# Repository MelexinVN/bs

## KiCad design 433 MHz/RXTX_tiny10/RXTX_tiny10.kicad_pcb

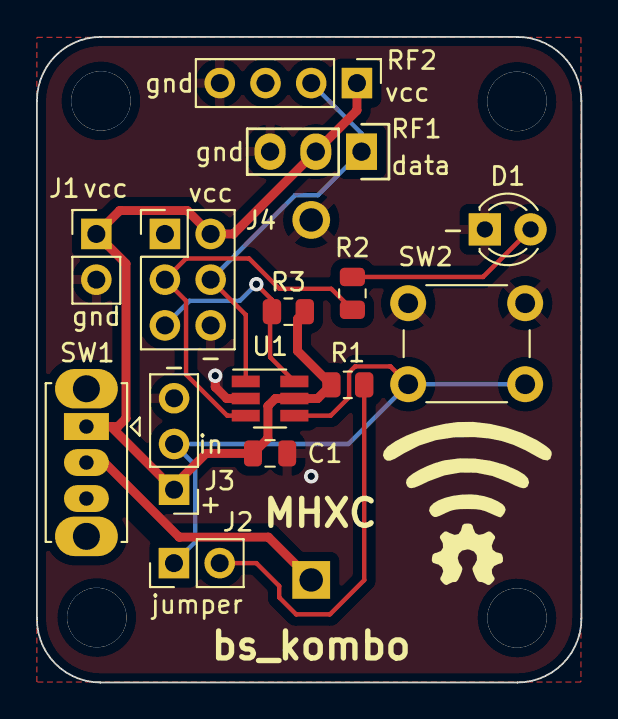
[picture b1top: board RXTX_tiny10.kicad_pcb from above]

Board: 2 copper layers, 30.3 x 35.9 mm, 15 parts (1 on the bottom side), 9 nets.

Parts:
BT?: Battery_Cell; BatteryHolder_ComfortableElectronic_CH273-2450_1x2450
C1: 100n; C_0805_2012Metric
D1: SFH4346; LED_D3.0mm
J1, J1#2: Conn_01x02; PinHeader_1x02_P2.54mm_Vertical
J3: Conn_01x03; PinHeader_1x03_P2.54mm_Vertical
J?: AVR-ISP-6; PinHeader_2x03_P2.54mm_Vertical
R?: 4.7K; R_0805_2012Metric
R?#2, R?#3: 4.7K; R_0805_2012Metric
RF1: RF_Transmitter_433_MHz
RF2: RF_Receiver_433_MHz; PinHeader_1x04_P2.54mm_Vertical
SW1: SW_DPDT_x2; SW_Slide_1P2T_CK_OS102011MS2Q
SW2: SW_Push_Dual_x2; SW_PUSH_6mm_H4.3mm
U1: ATtiny10-TS; SOT-23-6_Handsoldering

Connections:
+3V3: C1.1, J1#2.1, J3.1, J?.2 (VCC), R?.2, R?#2.2, RF1.2 (VCC), RF2.1 (VCC), SW1.1 (A), U1.5 (VCC)
GND: BT?.2 (-), C1.2, D1.1 (K), J1#2.2, J3.3, J?.6 (GND), RF1.3 (GND), RF2.4 (GND), SW2.2 (D), U1.2 (GND)
unnamed: BT?.1 (+), SW1.2 (B)
unnamed: D1.2 (A), R?#3.1
unnamed: J1.1, J3.2, SW2.1 (C), U1.4 (PB2)
unnamed: J1.2, R?.1
unnamed: J?.3 (SCK), R?#3.2, U1.3 (PB1)
unnamed: J?.4 (MOSI), RF1.1 (DATA), RF2.2 (DATA), U1.1 (PB0)
unnamed: J?.5 (~RST), R?#2.1, U1.6 (~RESET/PB3)

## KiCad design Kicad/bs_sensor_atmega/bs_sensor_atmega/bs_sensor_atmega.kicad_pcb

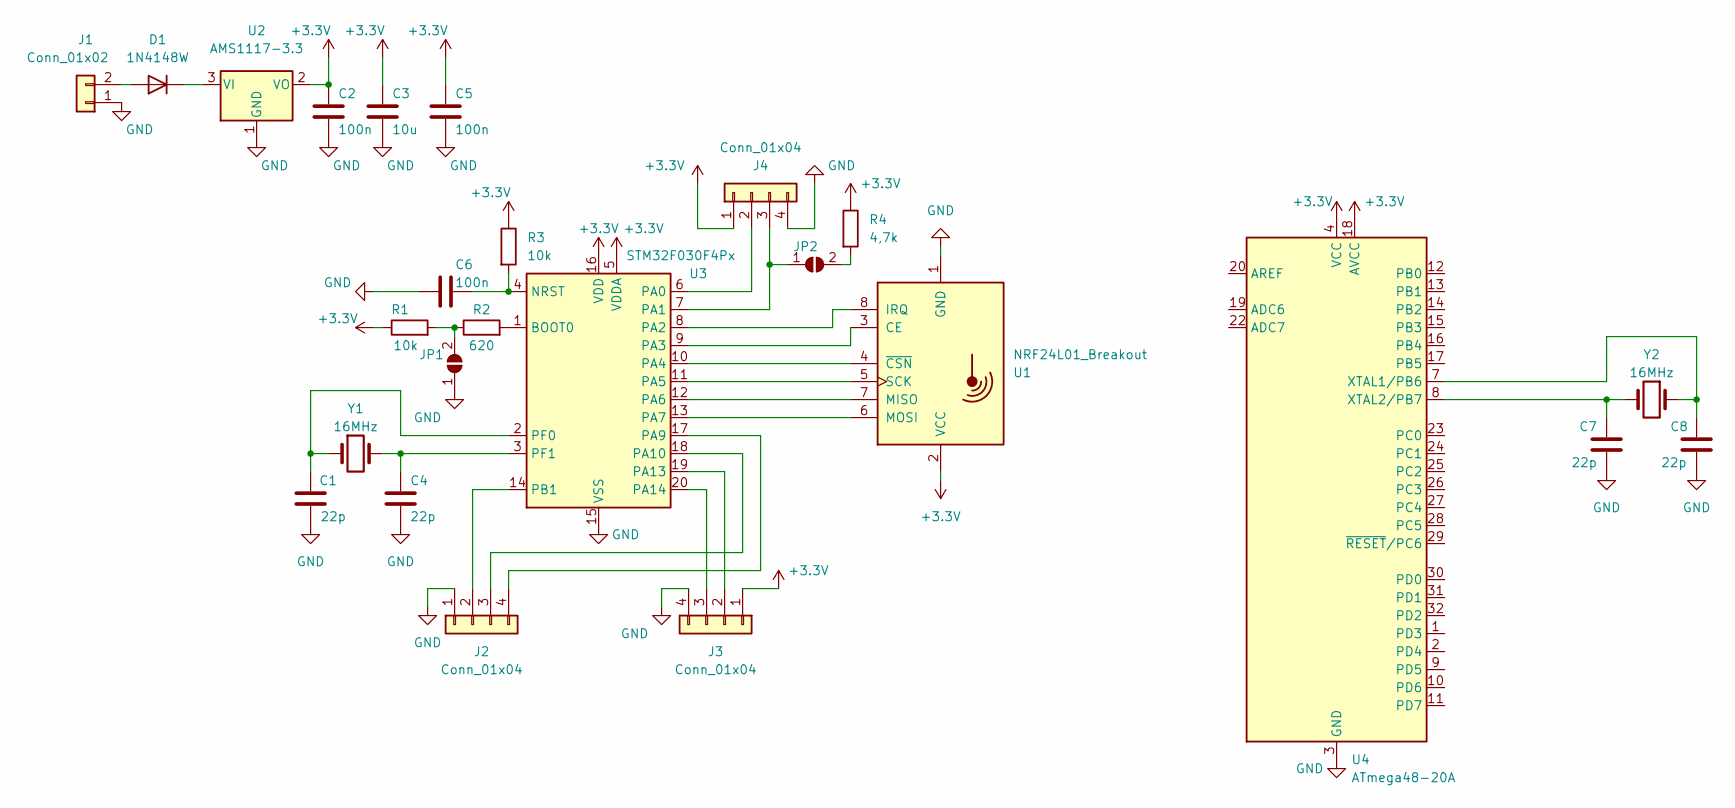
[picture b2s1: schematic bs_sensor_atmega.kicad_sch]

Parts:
C1, C4, C7, C8: 22p; C_0805_2012Metric
C2, C5, C6: 100n; C_0805_2012Metric
C3: 10u; C_0805_2012Metric
D1: 1N4148W; D_SOD-123
J1: Conn_01x02; PinHeader_1x02_P2.54mm_Vertical
J2, J3, J4: Conn_01x04; PinHeader_1x04_P2.54mm_Vertical
JP1, JP2: SolderJumper_2_Open; SolderJumper-2_P1.3mm_Open_TrianglePad1.0x1.5mm
R1, R3: 10k; R_0805_2012Metric
R2: 620; R_0603_1608Metric
R4: 4,7k; R_0805_2012Metric
U1: NRF24L01_Breakout; nRF24L01_Breakout
U2: AMS1117-3.3; SOT-223-3_TabPin2
U3: STM32F030F4Px; TSSOP-20_4.4x6.5mm_P0.65mm
U4: ATmega48-20A; TQFP-32_7x7mm_P0.8mm
Y1, Y2: 16MHz; Crystal_HC49-U_Vertical

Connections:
+3V3: C2.1, C3.1, C5.1, J3.1, J4.1, R1.1, R3.1, R4.1, U1.2 (VCC), U2.2 (VO), U3.5 (VDDA), U3.16 (VDD), U4.4 (VCC), U4.6 (VCC), U4.18 (AVCC)
GND: C1.1, C2.2, C3.2, C4.2, C5.2, C6.2, C7.2, C8.1, J1.1, J2.1, J3.4, J4.4, JP1.1 (A), U1.1 (GND), U2.1 (GND), U3.15 (VSS), U4.3 (GND), U4.5 (GND), U4.21 (GND)
unnamed: C1.2, U3.2 (PF0), Y1.1
unnamed: C4.1, U3.3 (PF1), Y1.2
unnamed: C6.1, R3.2, U3.4 (NRST)
unnamed: C7.1, U4.8 (XTAL2/PB7), Y2.2
unnamed: C8.2, U4.7 (XTAL1/PB6), Y2.1
unnamed: D1.1 (K), U2.3 (VI)
unnamed: D1.2 (A), J1.2
unnamed: J2.2, U3.14 (PB1)
unnamed: J2.3, U3.18 (PA10)
unnamed: J2.4, U3.17 (PA9)
unnamed: J3.2, U3.19 (PA13)
unnamed: J3.3, U3.20 (PA14)
unnamed: J4.2, U3.6 (PA0)
unnamed: J4.3, JP2.1 (A), U3.7 (PA1)
unnamed: JP1.2 (B), R1.2, R2.1
unnamed: JP2.2 (B), R4.2
unnamed: R2.2, U3.1 (BOOT0)
unnamed: U1.3 (CE), U3.9 (PA3)
unnamed: U1.4 (~CSN), U3.10 (PA4)
unnamed: U1.5 (SCK), U3.11 (PA5)
unnamed: U1.6 (MOSI), U3.13 (PA7)
unnamed: U1.7 (MISO), U3.12 (PA6)
unnamed: U1.8 (IRQ), U3.8 (PA2)

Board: 2 copper layers, 25 parts (0 on the bottom side), 25 nets, no tracks yet.

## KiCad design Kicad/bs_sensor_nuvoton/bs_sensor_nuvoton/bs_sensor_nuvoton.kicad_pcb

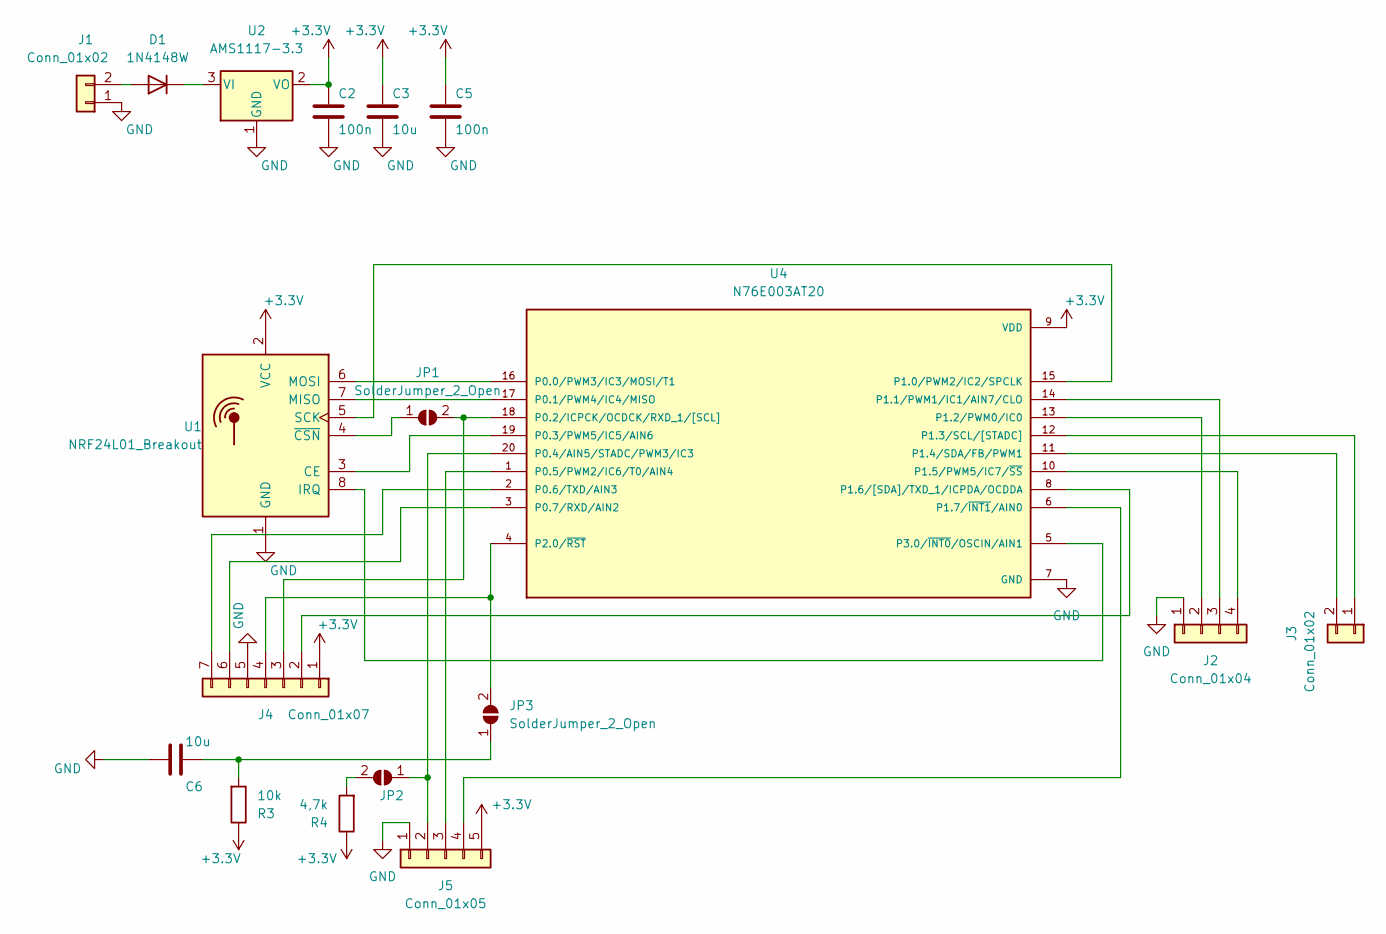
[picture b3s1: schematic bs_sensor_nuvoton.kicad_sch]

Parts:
C2, C5: 100n; C_0805_2012Metric
C3, C6: 10u; C_0805_2012Metric
D1: 1N4148W; D_SOD-123
J1, J3: Conn_01x02; PinHeader_1x02_P2.54mm_Vertical
J2: Conn_01x04; PinHeader_1x04_P2.54mm_Vertical
J4: Conn_01x07; PinHeader_1x07_P2.54mm_Vertical
J5: Conn_01x05; PinHeader_1x05_P2.54mm_Vertical
JP1, JP2, JP3: SolderJumper_2_Open; SolderJumper-2_P1.3mm_Open_TrianglePad1.0x1.5mm
R3: 10k; R_0805_2012Metric
R4: 4,7k; R_0805_2012Metric
U1: NRF24L01_Breakout; nRF24L01_Breakout
U2: AMS1117-3.3; SOT-223-3_TabPin2
U4: N76E003AT20; SOP65P640X120-20N; PARTREV 1.04

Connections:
+3V3: C2.1, C3.1, C5.1, J4.1, J5.5, R3.1, R4.1, U1.2 (VCC), U2.2 (VO), U4.9 (VDD)
GND: C2.2, C3.2, C5.2, C6.2, J1.1, J2.1, J4.5, J5.1, U1.1 (GND), U2.1 (GND), U4.7 (GND)
unnamed: C6.1, JP3.1 (A), R3.2
unnamed: D1.1 (K), U2.3 (VI)
unnamed: D1.2 (A), J1.2
unnamed: J2.2, U4.13 (P1.2/PWM0/IC0)
unnamed: J2.3, U4.14 (P1.1/PWM1/IC1/AIN7/CLO)
unnamed: J2.4, U4.10 (P1.5/PWM5/IC7/~SS)
unnamed: J3.1, U4.12 (P1.3/SCL/[STADC])
unnamed: J3.2, U4.11 (P1.4/SDA/FB/PWM1)
unnamed: J4.2, U4.8 (P1.6/[SDA]/TXD_1/ICPDA/OCDDA)
unnamed: J4.3, JP1.2 (B), U4.18 (P0.2/ICPCK/OCDCK/RXD_1/[SCL])
unnamed: J4.4, JP3.2 (B), U4.4 (P2.0/~RST)
unnamed: J4.6, U4.3 (P0.7/RXD/AIN2)
unnamed: J4.7, U4.2 (P0.6/TXD/AIN3)
unnamed: J5.2, JP2.1 (A), U4.20 (P0.4/AIN5/STADC/PWM3/IC3)
unnamed: J5.3, U4.1 (P0.5/PWM2/IC6/T0/AIN4)
unnamed: J5.4, U4.6 (P1.7/~INT1/AIN0)
unnamed: JP1.1 (A), U1.4 (~CSN)
unnamed: JP2.2 (B), R4.2
unnamed: U1.3 (CE), U4.19 (P0.3/PWM5/IC5/AIN6)
unnamed: U1.5 (SCK), U4.15 (P1.0/PWM2/IC2/SPCLK)
unnamed: U1.6 (MOSI), U4.16 (P0.0/PWM3/IC3/MOSI/T1)
unnamed: U1.7 (MISO), U4.17 (P0.1/PWM4/IC4/MISO)
unnamed: U1.8 (IRQ), U4.5 (P3.0/~INT0/OSCIN/AIN1)

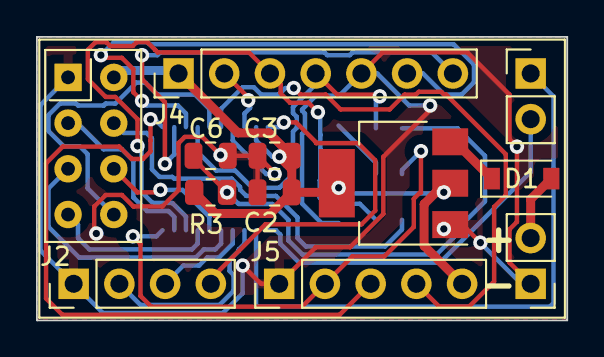
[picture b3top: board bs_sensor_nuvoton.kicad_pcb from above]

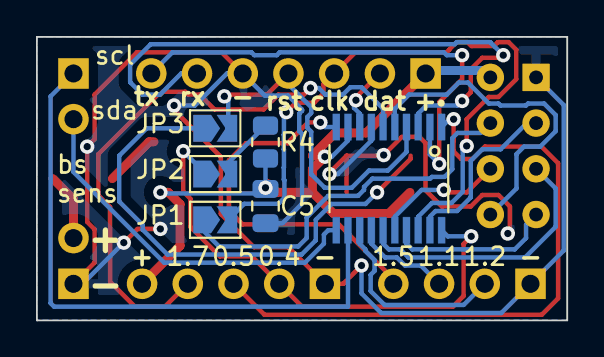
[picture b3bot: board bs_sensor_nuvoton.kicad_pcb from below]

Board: 2 copper layers, 29.5 x 15.7 mm, 18 parts (6 on the bottom side), 25 nets.

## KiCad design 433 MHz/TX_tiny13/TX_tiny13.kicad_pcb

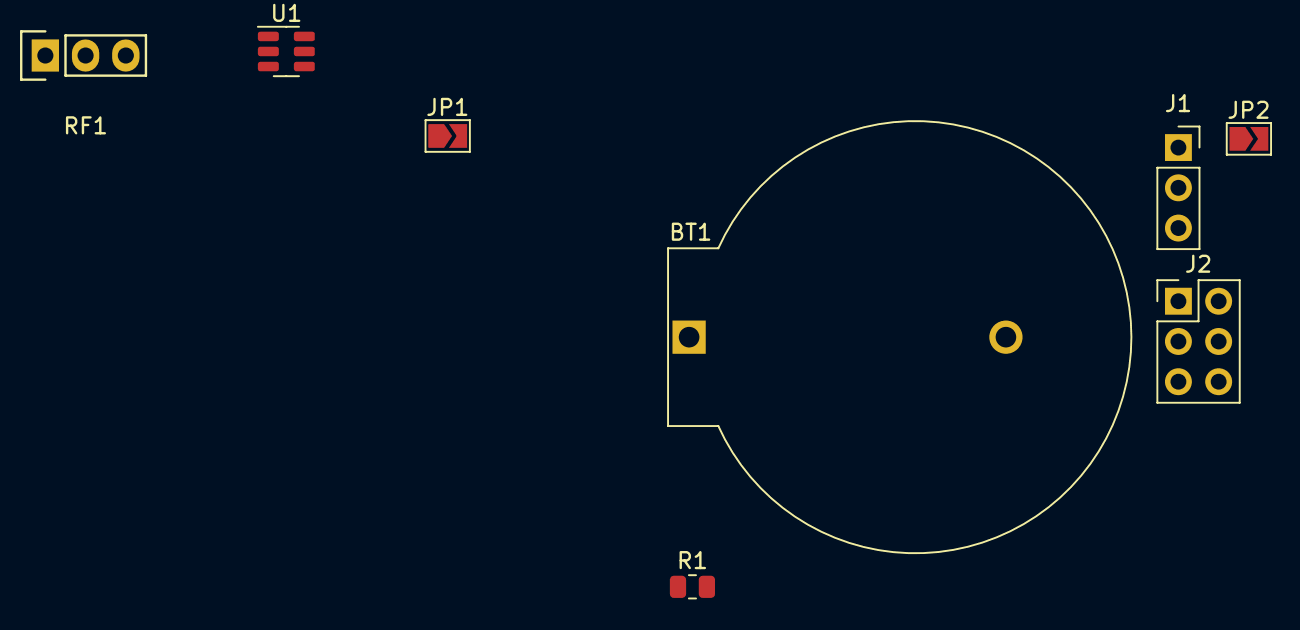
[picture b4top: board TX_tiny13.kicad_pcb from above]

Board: 2 copper layers, 8 parts (0 on the bottom side), 8 nets, no tracks yet.

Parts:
BT?: Battery_Cell; BatteryHolder_ComfortableElectronic_CH273-2450_1x2450
J?: AVR-ISP-6; PinHeader_2x03_P2.54mm_Vertical
J?#2: Conn_01x03; PinSocket_1x03_P2.54mm_Vertical
JP1: SolderJumper_2_Open; SolderJumper-2_P1.3mm_Open_TrianglePad1.0x1.5mm
JP?: SolderJumper_2_Open; SolderJumper-2_P1.3mm_Open_TrianglePad1.0x1.5mm
R?: 4.7K; R_0805_2012Metric
RF1: RF_Transmitter_433_MHz
U1: ATtiny10-TS; SOT-23-6

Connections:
+3V3: BT?.1 (+), J?.2 (VCC), J?#2.1, R?.2, RF1.2 (VCC), U1.5 (VCC)
GND: BT?.2 (-), J?.6 (GND), J?#2.3, RF1.3 (GND), U1.2 (GND)
unnamed: J?#2.2, JP1.2 (B), U1.4 (PB2)
unnamed: J?.3 (SCK), U1.3 (PB1)
unnamed: J?.4 (MOSI), JP?.1 (A), U1.1 (PB0)
unnamed: J?.5 (~RST), U1.6 (~RESET/PB3)
unnamed: JP1.1 (A), R?.1
unnamed: JP?.2 (B), RF1.1 (DATA)

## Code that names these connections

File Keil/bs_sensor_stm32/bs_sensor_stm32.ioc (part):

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Mcu.Name=STM32F030F4Px
Mcu.Package=TSSOP20
Mcu.UserName=STM32F030F4Px
PA10.Signal=GPIO_Output
PA13.Mode=Serial_Wire
PA13.Signal=SYS_SWDIO
PA14.Mode=Serial_Wire
PA14.Signal=SYS_SWCLK
PA2.Signal=GPXTI2
PA3.Signal=GPIO_Output
PA4.Signal=GPIO_Output
PA5.Mode=Full_Duplex_Master
PA5.Signal=SPI1_SCK
PA6.Mode=Full_Duplex_Master
PA6.Signal=SPI1_MISO
PA7.Mode=Full_Duplex_Master
PA7.Signal=SPI1_MOSI
PA9.Signal=GPIO_Output
PB1.Signal=GPIO_Output
PF0-OSC_IN.Mode=HSE-External-Oscillator
PF0-OSC_IN.Signal=RCC_OSC_IN
PF1-OSC_OUT.Mode=HSE-External-Oscillator
PF1-OSC_OUT.Signal=RCC_OSC_OUT
RCC.HSE_VALUE=16000000
RCC.SYSCLKFreq_VALUE=48000000
RCC.SYSCLKSource=RCC_SYSCLKSOURCE_PLLCLK
board=custom

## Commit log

2022-02-15 Беспроводная система 15.02.2022
2022-02-16 16.02.2022
2022-02-16 Create git_test
2022-02-18 18.02.2022
2022-03-01 01.03.2022
2022-03-05 05.03.2022
2022-03-07 07.09.2022
2022-03-07 07.03.2022
2022-03-08 08.03.2022
2022-03-16 16.03.2022
2022-03-22 22.03.2022
2022-03-25 25.03.2022
2022-03-28 28.03.2022
2022-03-29 29.03.2022
2022-03-31 31.03.2022
2022-04-01 01.04.2022
2022-04-04 04.04.2022
2022-04-05 05.04.2022
2022-04-07 07.04.2022
2022-04-08 08.04.2022
2022-04-11 11.04.2022
2022-04-12 12.04.2022
2022-04-13 13.04.2022
2022-04-15 15.04.2022
2022-04-20 20.04.2022
2022-04-21 21.04.2022
2022-04-22 22.04.2022
2022-04-25 25.04.2022
2022-04-26 26.04.2022
2022-04-29 29.04.2022
2022-05-05 05.05.2022
2022-05-06 06.05.2022
2022-05-13 13.05.2022
2022-05-18 18.05.2022
2022-05-20 20.05.2022
2022-05-20 kicad models
2022-05-23 23.05.2022
2022-05-26 26.05.2022
2022-05-27 27.05.2022
2022-05-28 28.05.2022
2022-06-01 01.06.2022
2022-06-03 03.02.2022
2022-06-09 09.06.2022
2022-06-10 10.06.2022
2022-06-14 14.06.2022
2022-06-15 15.06.2022
2022-06-21 21.06.2022
2022-06-23 23.06.2022
2022-06-24 24.06.2022
2022-06-26 26.06.2022
2022-06-30 30.06.2022
2022-07-01 01.07.2022
2022-07-05 05.07.2022
2022-07-07 07.07.2022
2022-07-08 08.07.2022
2022-07-11 11.07.2022
2022-07-12 12.07.2022
2022-07-13 13.07.2022
2022-07-14 14.07.2022
2022-07-15 15.07.2022
